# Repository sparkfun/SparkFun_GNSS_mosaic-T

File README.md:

SparkFun Timing GNSS Breakout - mosaic-T
========================================

[*SparkFun Timing GNSS Breakout - mosaic-T (GPS-28731)*](https://www.sparkfun.com/sparkfun-timing-gnss-breakout-mosaic-t.html)

At the heart of our Timing GNSS Breakout is [Septentrio](https://www.septentrio.com/en)'s mosaic-T, a compact, ultra-low power, multi-band, multi-constellation, high-precision GNSS timing receiver. It can acheive a timing precision of 5ns (5 billionths of a second), or better than 1ns with an optional subscription to the Fugro AtomiChron® L-band timing service. Event accuracy is better than 20ns. It also features Septentrio's unique [AIM+ technology](https://www.septentrio.com/en/learn-more/advanced-positioning-technology/aim-jamming-protection) for interference mitigation and anti-spoofing, ensuring best-in-class reliability and accuracy.

This board provides easy access to the mosaic-T's reference clock. Want to create your own disciplined oscillator? With this board you can. You can use the `RxClkBias` from the mosaic-T `PVTCartesian` or `PVTGeodetic` SBF messages to discipline your own 10MHz oscillator. The *EXT REF* connector accepts 50 Ohm 10MHz signals in the range -14dBm (min) to +14dBm (max). The *INT EXT* slide switch selects the internal or external oscillator.

The mosaic-T is a sophisticated timing receiver running an internal web server that can be accessed through the USB interface with a standard browser using a Linux/Windows computer. Septentrio also provides dozens of [video tutorials](https://www.youtube.com/@SeptentrioGNSS/videos) to guide users through the configuration settings of their GNSS receivers utilizing the web interface.

Beyond the capabilities of the mosaic-T module, this board is seamless to operate with no programming skills required. Gone are the times when a microcontroller was required to interface with the GNSS receiver and log data to an SD card and when users had to carry around an SD card reader to extract the data from the SD card. The Timing GNSS Breakout - mosaic-T  can start/stop logging data or mount/unmount the SD card, without a single line of code, just utilizing a simple button. For the users who prefer a command-line interface, Septentrio has you covered. Users can still control and configure the mosaic-T module through a CLI, which is useful for scenarios such as production line testing *(in fact, that is how we tested this board)*.

This breakout board is a perfect middle ground for users who would like to integrate the mosaic-T module into a project/enclosure with access to a majority of the module's available pins, similar to Septentrio's developer kit, but in the smaller form factor of their evaluation kit. Or maybe... you just needed a very accurate PPS output at a 3.3V logic level. *Please, check out our [hookup guide](https://docs.sparkfun.com/SparkFun_GNSS_mosaic-T) for more details on the capabilities of this board (that we couldn't fit in this product description).*

> [!CAUTION]
>
> RTK Not Supported
> --------------
> The mosaic-T is a superb GNSS module designed for highly accurate timing applications. **But it does not support RTK. It can not be configured as a RTK Rover or Base. RTCM output is not supported.**

Documentation
-------------

- **[Hookup Guide (mkdocs)](http://docs.sparkfun.com/SparkFun_GNSS_mosaic-T/)** - A hookup guide for the SparkFun mosaic-T Timing GNSS breakout board hosted by GitHub pages.<br>

Repository Contents
-------------------

- **[/docs](/docs/)** - Online documentation files
  - [/assets](/docs/assets/) - Assets files
    - [/3d_model](/docs/assets/3d_model/) - 3D models for the board
    - [/board_files](/docs/assets/board_files/) - Design files for the board
      - [KiCad Design Files](/docs/assets/board_files/kicad_files.zip) (.zip)
      - [Schematic](/docs/assets/board_files/schematic.pdf) (.pdf)
      - [Dimensions](/docs/assets/board_files/dimensions.pdf) (.pdf)
    - [/component_documentation](/docs/assets/component_documentation/) - Datasheets for hardware components
    - [/img/hookup_guide](/docs/assets/img/hookup_guide/) - Images for hookup guide documentation - Hookup guide images for the board
    - /Hardware - Hardware design files (.brd, .sch)
      - /Production - Production files

Product Variants
----------------

- mosaic-T:
  - [GPS-28731](https://www.sparkfun.com/sparkfun-timing-gnss-breakout-mosaic-t.html) - mosaic-T Timing GNSS Breakout
  - [SXT](https://www.sparkpnt.com/products/sxt-gnssdo) - GNSS Disciplined Oscillator
- mosaic-X5:
  - [GPS-23088](https://www.sparkfun.com/sparkfun-triband-gnss-rtk-breakout-mosaic-x5.html) - Triband GNSS RTK Breakout - mosaic-X5
  - [SXM-E](https://www.sparkpnt.com/products/sparkpnt-sxm-e-cors) - RTK mosaic-X5
  - [GPS-24903](https://www.sparkfun.com/sparkpnt-rtk-facet-mosaic-l-band.html) - SparkPNT RTK Facet mosaic L-Band
  - Flex Modules:
    - [GPS-28138](https://www.sparkfun.com/sparkpnt-gnss-flex-module-mosaic-x5.html) - GNSS Flex module - mosaic-X5
    - [GPS-29457](https://www.sparkfun.com/sparkpnt-gnss-flex-module-mosaic-x5-im19-imu.html) - GNSS Flex module - mosaic-X5 & IM19
    - [GPS-28766](https://www.sparkfun.com/sparkfun-gnss-flex-phat-mosaic-x5.html) - GNSS Flex pHAT w/ the mosaic-X5 GNSS Flex module
    - [GPS-29889](https://www.sparkfun.com/sparkfun-gnss-flex-phat-mosaic-x5-im19-imu.html) - GNSS Flex pHAT w/ the mosaic-X5 & IM19 GNSS Flex module
- mosaic-G5 P3:
  - [GPS-29208]( - GNSS RTK Breakout - mosaic-G5 P3
  - Flex Modules:
    - [GPS-29209](https://www.sparkfun.com/sparkpnt-gnss-flex-module-mosaic-g5-p3.html) - GNSS Flex module - mosaic-G5 P3
    - [GPS-29363](https://www.sparkfun.com/sparkpnt-gnss-flex-module-mosaic-g5-p3-im19-imu.html) - GNSS Flex module - mosaic-G5 P3 & IM19
    - [GPS-](https://www.sparkfun.com/sparkfun-gnss-flex-phat-mosaic-g5-p3.html) - GNSS Flex pHAT w/ the mosaic-G5 P3 GNSS Flex module
    - [GPS-](https://www.sparkfun.com/sparkfun-gnss-flex-phat-mosaic-g5-p3-im19-imu.html) - GNSS Flex pHAT w/ the mosaic-G5 P3 & IM19 GNSS Flex module

Version History
---------------

- [v10](https://github.com/sparkfun/SparkFun_GNSS_mosaic-T/releases/tag/v10) - Initial Release

License Information
-------------------

This product is ***open source***!

Please review the [`LICENSE.md`](./LICENSE.md) file for license information.

If you have any questions or concerns about licensing, please contact technical support on our [SparkFun forums](https://community.sparkfun.com/).

Distributed as-is; no warranty is given.

- Your friends at SparkFun.

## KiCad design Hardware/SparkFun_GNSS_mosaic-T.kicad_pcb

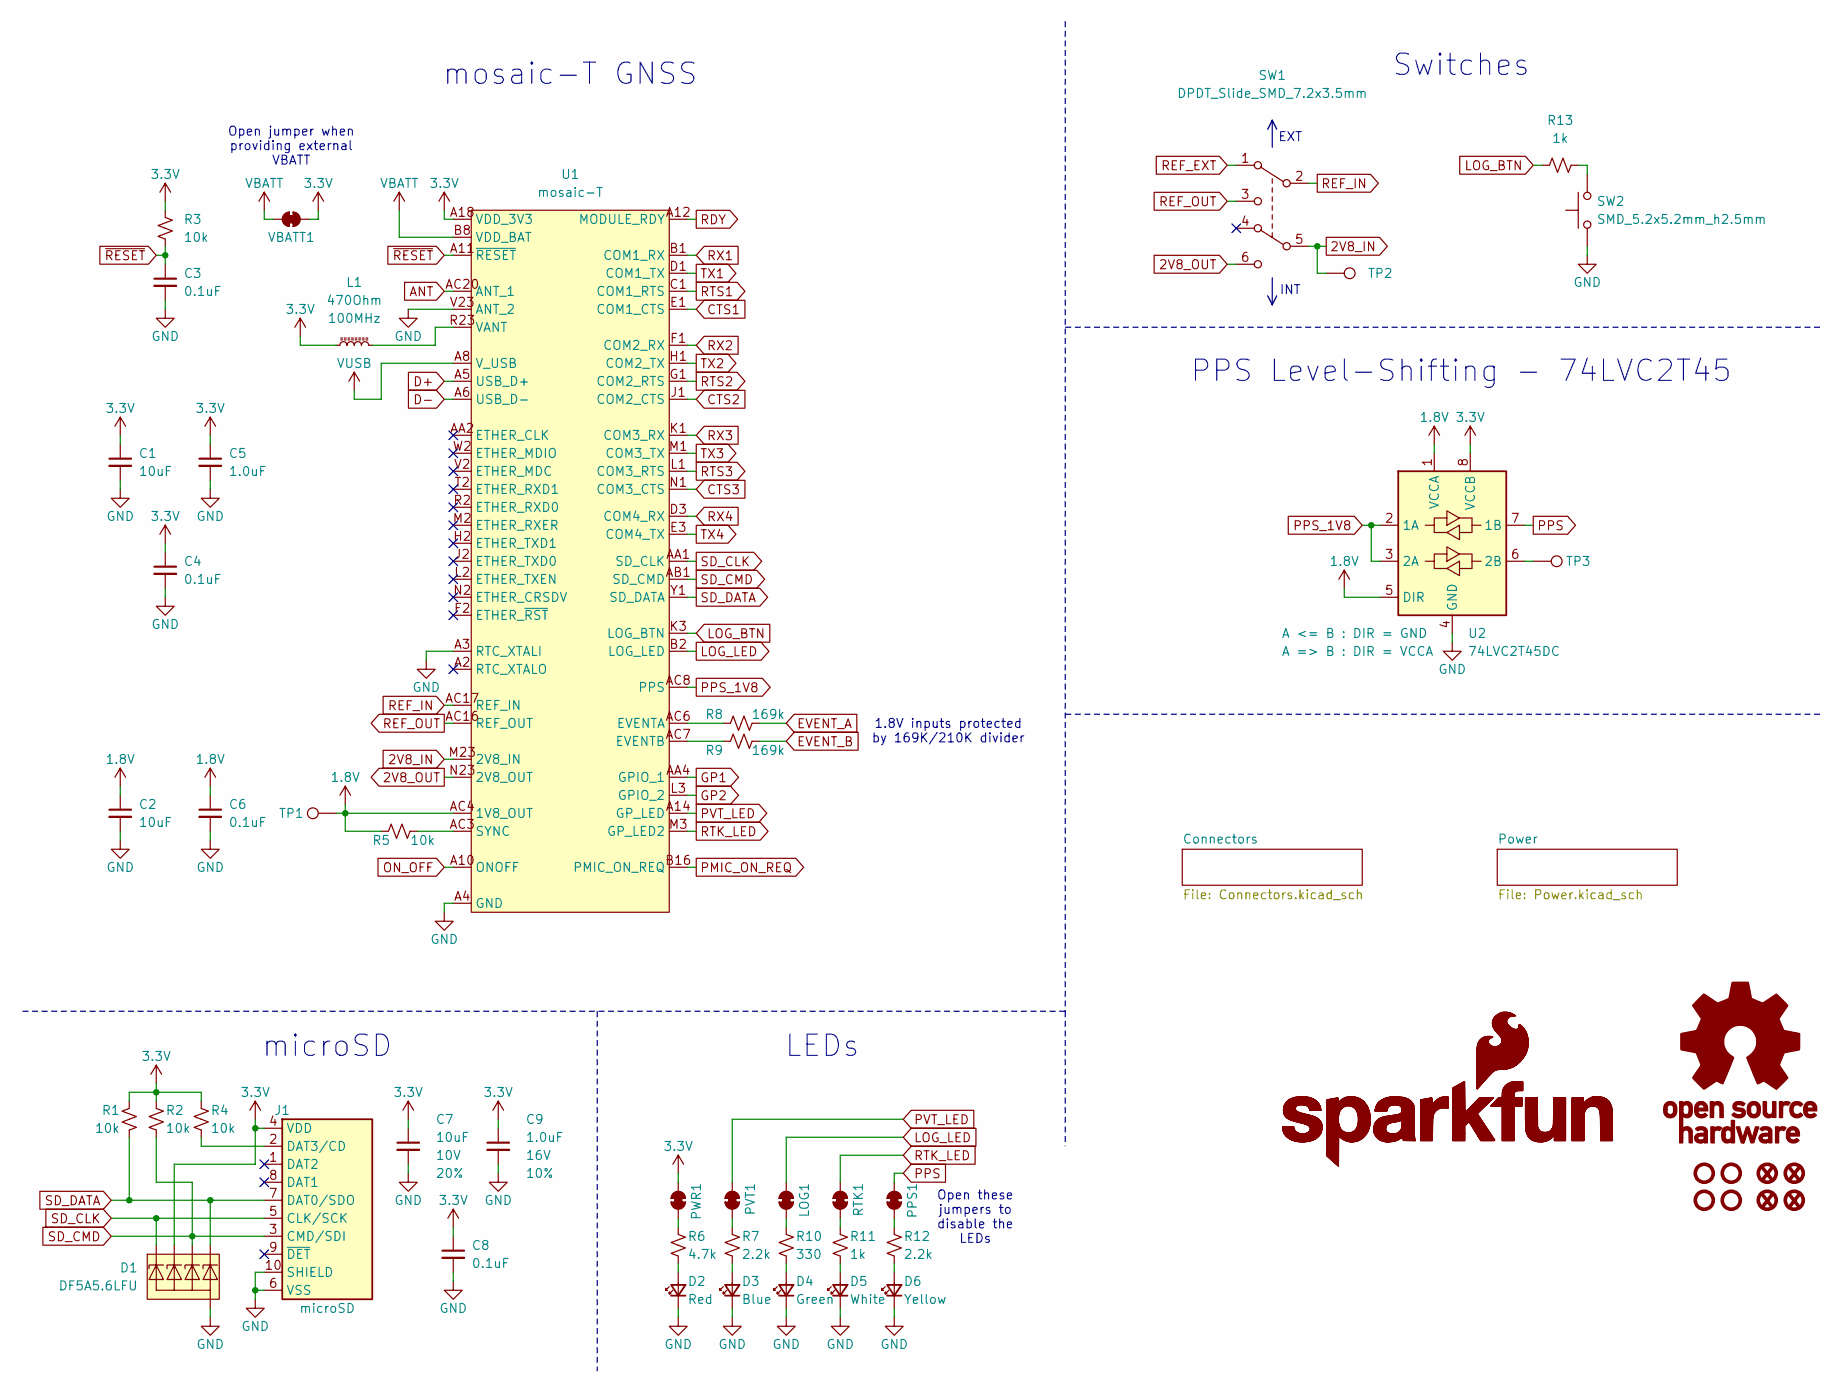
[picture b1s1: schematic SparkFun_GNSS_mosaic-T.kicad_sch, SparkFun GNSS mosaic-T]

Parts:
C1, C2, C7: 10uF; C_0603_1608Metric; Voltage 10V; Tolerance 20%
C3, C4, C6, C8: 0.1uF; C_0603_1608Metric; Voltage 25V; Tolerance 20%
C5, C9: 1.0uF; C_0603_1608Metric; Voltage 16V; Tolerance 10%
D1: DF5A5.6LFU; SOT-353
D2: Red; LED_0603_1608Metric_Red
D3: Blue; LED_0603_1608Metric_Blue
D4: Green; LED_0603_1608Metric_Green
D5: White; LED_0603_1608Metric_White
D6: Yellow; LED_0603_1608Metric_Yellow
FID1, FID2, FID3, FID4: Fiducial_0.5mm; Fiducial_0.5mm_Mask1mm
G1, G2: SparkFun_Logo
G3: OSHW_Logo; Creative_Commons_License
J1: microSD; microSD_External_Pin
L1: 470Ohm; C_0603_1608Metric
LOG1: Jumper_2_NC_Trace
PPS1: Jumper_2_NC_Trace
PVT1: Jumper_2_NC_Trace
PWR1: Jumper_2_NC_Trace
R1, R2, R3, R4, R5: 10k; R_0603_1608Metric
R6: 4.7k; R_0603_1608Metric
R7, R12: 2.2k; R_0603_1608Metric
R8, R9: 169k; R_0603_1608Metric
R10: 330; R_0603_1608Metric
R11, R13: 1k; R_0603_1608Metric
RTK1: Jumper_2_NC_Trace
ST1, ST2, ST3, ST4: Standoff
SW1: DPDT_Slide_SMD_7.2x3.5mm; Slide_DPDT_SMD_7.2x3.5mm; Mfg Part# ABC
SW2: SMD_5.2x5.2mm_h2.5mm; Push_SMD_5.2x5.2mm_h2.5mm
TP1, TP2, TP3: 1.25mm; TestPoint-1.25mm
U1: mosaic-T; MOSAIC_LGA
U2: 74LVC2T45DC; VSSOP8_SOT765-1
VBATT1: Jumper_2_NC_Trace

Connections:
1.8V: C2.1, C6.1, R5.1, TP1.1, U1.AC4 (1V8_OUT), U2.1 (VCCA), U2.5 (DIR); also elsewhere on the board
2V8_IN: SW1.5 (B), TP2.1, U1.M23 (2V8_IN)
2V8_OUT: SW1.6 (C), U1.N23 (2V8_OUT)
3.3V: C1.1, C4.1, C5.1, C7.1, C8.1, C9.1, D1.3 (K2), J1.4 (VDD), L1.1, PWR1.2 (B), R1.2, R2.2, R3.2, R4.2, U1.A18 (VDD_3V3), U1.A19 (VDD_3V3), U1.A20 (VDD_3V3), U1.B18 (VDD_3V3), U1.B19 (VDD_3V3), U1.B20 (VDD_3V3), U1.C18 (VDD_3V3), U1.C19 (VDD_3V3), U1.C20 (VDD_3V3), U2.8 (VCCB), VBATT1.1 (A); also elsewhere on the board
ANT: U1.AC20 (ANT_1); also elsewhere on the board
CTS1: U1.E1 (COM1_CTS); also elsewhere on the board
CTS2: U1.J1 (COM2_CTS); also elsewhere on the board
CTS3: U1.N1 (COM3_CTS); also elsewhere on the board
D+: U1.A5 (USB_D+); also elsewhere on the board
D-: U1.A6 (USB_D-); also elsewhere on the board
EVENT_A: R8.2; also elsewhere on the board
EVENT_B: R9.2; also elsewhere on the board
GND: C1.2, C2.2, C3.2, C4.2, C5.2, C6.2, C7.2, C8.2, C9.2, D1.2 (A), D2.1 (K), D3.1 (K), D4.1 (K), D5.1 (K), D6.1 (K), J1.6 (VSS), J1.10 (SHIELD), SW2.1, U1.A3 (RTC_XTALI), U1.A4 (GND), U1.A7 (GND), U1.A15 (GND), U1.A16 (GND), U1.A17 (GND), U1.A21 (GND), U1.A22 (GND), U1.A23 (GND), U1.AA13 (GND), U1.AA14 (GND), U1.AA15 (GND), U1.AA16 (GND), U1.AA17 (GND), U1.AA18 (GND), U1.AA19 (GND), U1.AA20 (GND), U1.AA21 (GND), U1.AA22 (GND), U1.AA23 (GND), U1.AB2 (GND), U1.AB3 (GND), U1.AB4 (GND), U1.AB5 (GND), U1.AB6 (GND), U1.AB7 (GND), U1.AB8 (GND), U1.AB13 (GND), U1.AB14 (GND), U1.AB15 (GND), U1.AB16 (GND), U1.AB17 (GND), U1.AB18 (GND), U1.AB19 (GND), U1.AB20 (GND), U1.AB21 (GND), U1.AB22 (GND), U1.AB23 (GND), U1.AC13 (GND), U1.AC15 (GND), U1.AC18 (GND), U1.AC19 (GND), U1.AC21 (GND), U1.AC22 (GND), U1.AC23 (GND), U1.B4 (GND), U1.B5 (GND), U1.B6 (GND), U1.B7 (GND), U1.B13 (GND), U1.B17 (GND), U1.B21 (GND), U1.C4 (GND), U1.C7 (GND), U1.C15 (GND), U1.C16 (GND), U1.C17 (GND), U1.C23 (GND), U1.D2 (GND), U1.D21 (GND), U1.D22 (GND), U1.D23 (GND), U1.E2 (GND), U1.E21 (GND), U1.E22 (GND), U1.E23 (GND), U1.F21 (GND), U1.F22 (GND), U1.F23 (GND), U1.G2 (GND), U1.G21 (GND), U1.G23 (GND), U1.H21 (GND), U1.H22 (GND), U1.H23 (GND), U1.J21 (GND), U1.J22 (GND), U1.J23 (GND), U1.K2 (GND), U1.K21 (GND), U1.K22 (GND), U1.K23 (GND), U1.L21 (GND), U1.L22 (GND), U1.L23 (GND), U1.M21 (GND), U1.M22 (GND), U1.N21 (GND), U1.N22 (GND), U1.P1 (GND), U1.P2 (GND), U1.P3 (GND), U1.P21 (GND), U1.P22 (GND), U1.R3 (GND), U1.R21 (GND), U1.R22 (GND), U1.T21 (GND), U1.T22 (GND), U1.T23 (GND), U1.U2 (GND), U1.U21 (GND), U1.U22 (GND), U1.U23 (GND), U1.V21 (GND), U1.V22 (GND), U1.V23 (ANT_2), U1.W21 (GND), U1.W22 (GND), U1.W23 (GND), U1.Y2 (GND), U1.Y21 (GND), U1.Y22 (GND), U1.Y23 (GND), U2.4 (GND); also elsewhere on the board
GP1: U1.AA4 (GPIO_1); also elsewhere on the board
GP2: U1.L3 (GPIO_2); also elsewhere on the board
LOG_BTN: R13.2, U1.K3 (LOG_BTN); also elsewhere on the board
LOG_LED: LOG1.2 (B), U1.B2 (LOG_LED); also elsewhere on the board
unnamed: D2.2 (A), R6.1
unnamed: D3.2 (A), R7.1
unnamed: D4.2 (A), R10.1
unnamed: D5.2 (A), R11.1
unnamed: D6.2 (A), R12.1
unnamed: J1.2 (DAT3/CD), R4.1
unnamed: LOG1.1 (A), R10.2
unnamed: PPS1.1 (A), R12.2
unnamed: PVT1.1 (A), R7.2
unnamed: PWR1.1 (A), R6.2
unnamed: R13.1, SW2.2
unnamed: R11.2, RTK1.1 (A)
unnamed: R8.1, U1.AC6 (EVENTA)
unnamed: R9.1, U1.AC7 (EVENTB)
unnamed: R5.2, U1.AC3 (SYNC)
unnamed: TP3.1, U2.6 (2B)
ON_OFF: U1.A10 (ONOFF); also elsewhere on the board
PMIC_ON_REQ: U1.B16 (PMIC_ON_REQ); also elsewhere on the board
PPS: PPS1.2 (B), U2.7 (1B); also elsewhere on the board
PPS_1V8: U1.AC8 (PPS), U2.2 (1A), U2.3 (2A)
PVT_LED: PVT1.2 (B), U1.A14 (GP_LED); also elsewhere on the board
RDY: U1.A12 (MODULE_RDY); also elsewhere on the board
REF_EXT: SW1.1 (A); also elsewhere on the board
REF_IN: SW1.2 (B), U1.AC17 (REF_IN)
REF_OUT: SW1.3 (C), U1.AC16 (REF_OUT)
RTK_LED: RTK1.2 (B), U1.M3 (GP_LED2); also elsewhere on the board
RTS1: U1.C1 (COM1_RTS); also elsewhere on the board
RTS2: U1.G1 (COM2_RTS); also elsewhere on the board
RTS3: U1.L1 (COM3_RTS); also elsewhere on the board
RX1: U1.B1 (COM1_RX); also elsewhere on the board
RX2: U1.F1 (COM2_RX); also elsewhere on the board
RX3: U1.K1 (COM3_RX); also elsewhere on the board
RX4: U1.D3 (COM4_RX); also elsewhere on the board
SD_CLK: D1.1 (K1), J1.5 (CLK/SCK), U1.AA1 (SD_CLK)
SD_CMD: D1.4 (K3), J1.3 (CMD/SDI), R2.1, U1.AB1 (SD_CMD)
SD_DATA: D1.5 (K4), J1.7 (DAT0/SDO), R1.1, U1.Y1 (SD_DATA)
TX1: U1.D1 (COM1_TX); also elsewhere on the board
TX2: U1.H1 (COM2_TX); also elsewhere on the board
TX3: U1.M1 (COM3_TX); also elsewhere on the board
TX4: U1.E3 (COM4_TX); also elsewhere on the board
VANT: L1.2, U1.P23 (VANT), U1.R23 (VANT)
VBATT: U1.B8 (VDD_BAT), VBATT1.2 (B); also elsewhere on the board
VUSB: U1.A8 (V_USB); also elsewhere on the board
~RESET: C3.1, R3.1, U1.A11 (~RESET); also elsewhere on the board

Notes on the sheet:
LEDs
PPS Level-Shifting - 74LVC2T45
Open jumper when providing external VBATT
mosaic-T GNSS
Switches
Open these jumpers to disable the LEDs
microSD
EXT
1.8V inputs protected by 169K/210K divider
INT

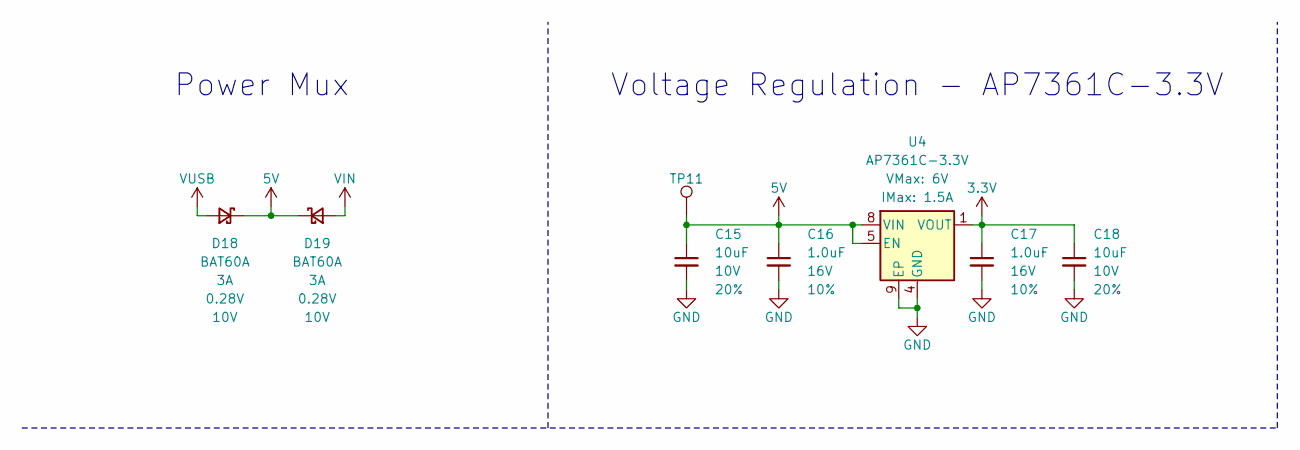
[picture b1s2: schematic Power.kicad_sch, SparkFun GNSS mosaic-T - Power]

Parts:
C15, C18: 10uF; C_0603_1608Metric; Voltage 10V; Tolerance 20%
C16, C17: 1.0uF; C_0603_1608Metric; Voltage 16V; Tolerance 10%
D18, D19: BAT60A; SOD-323
TP11: 1.25mm; TestPoint-1.25mm
U4: AP7361C-3.3V; UDFN-8

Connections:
3.3V: C17.1, C18.1, U4.1 (VOUT); also elsewhere on the board
5V: C15.1, C16.1, D18.1 (K), D19.1 (K), TP11.1, U4.5 (EN), U4.8 (VIN); also elsewhere on the board
GND: C15.2, C16.2, C17.2, C18.2, U4.4 (GND), U4.9 (EP); also elsewhere on the board
VIN: D19.2 (A); also elsewhere on the board
VUSB: D18.2 (A); also elsewhere on the board

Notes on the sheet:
Power Mux
Voltage Regulation - AP7361C-3.3V

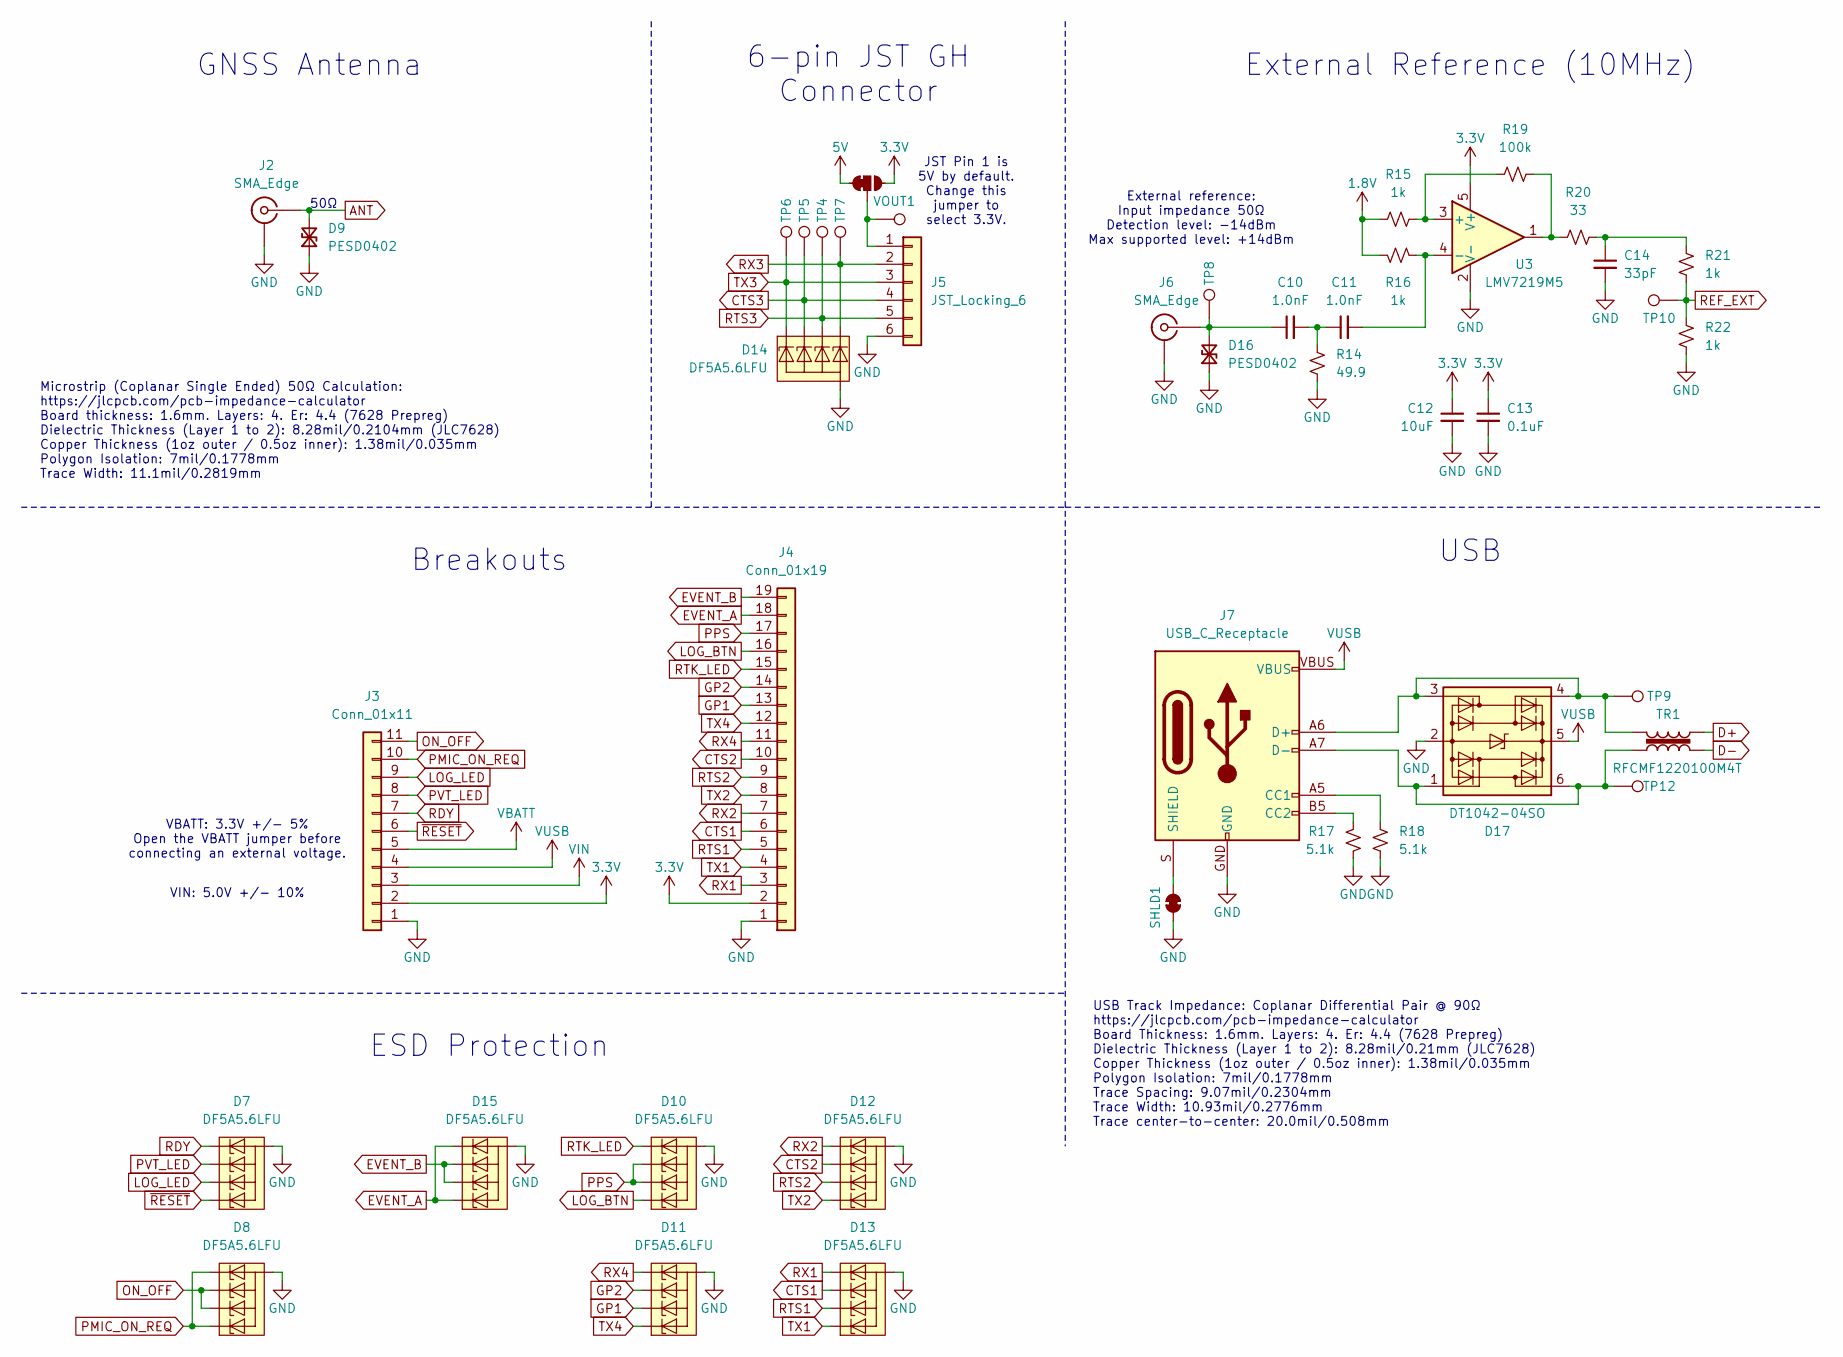
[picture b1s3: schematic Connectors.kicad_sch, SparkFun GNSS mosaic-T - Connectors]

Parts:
C10, C11: 1.0nF; C_0603_1608Metric; Voltage 50V; Tolerance 10%
C12: 10uF; C_0603_1608Metric; Voltage 10V; Tolerance 20%
C13: 0.1uF; C_0603_1608Metric; Voltage 25V; Tolerance 20%
C14: 33pF; C_0603_1608Metric; Voltage 50V; Tolerance 5%
D7, D8, D10, D11, D12, D13, D14, D15: DF5A5.6LFU; SOT-353
D9, D16: PESD0402; C_0402_1005Metric
D17: DT1042-04SO; SOT23-6
J2, J6: SMA_Edge
J3: Conn_01x11; 1x11
J4: Conn_01x19; 1x19
J5: JST_Locking_6; JST_SMD_1.25mm-6_Locking
J7: USB_C_Receptacle; USB-C_16
R14: 49.9; R_0603_1608Metric; Tolerance 1%
R15, R16, R21, R22: 1k; R_0603_1608Metric
R17, R18: 5.1k; R_0603_1608Metric
R19: 100k; R_0603_1608Metric
R20: 33; R_0603_1608Metric
SHLD1: Jumper_2_NC_Trace
TP4, TP5, TP6, TP7, TP8, TP9, TP10, TP12, TP13: 1.25mm; TestPoint-1.25mm
TR1: RFCMF1220100M4T
U3: LMV7219M5; SOT23-5
VOUT1: Jumper_3_NC-1_Trace

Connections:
1.8V: R15.2, R16.2; also elsewhere on the board
3.3V: C12.1, C13.1, J3.2, J4.2, U3.5 (V+), VOUT1.3 (C); also elsewhere on the board
5V: VOUT1.1 (A); also elsewhere on the board
ANT: D9.2 (A2), J2.1 (In); also elsewhere on the board
CTS1: D13.4 (K3), J4.6; also elsewhere on the board
CTS2: D12.4 (K3), J4.10; also elsewhere on the board
CTS3: D14.3 (K2), J5.4, TP5.1; also elsewhere on the board
D+: TR1.4; also elsewhere on the board
D-: TR1.2; also elsewhere on the board
EVENT_A: D15.1 (K1), D15.5 (K4), J4.18; also elsewhere on the board
EVENT_B: D15.3 (K2), D15.4 (K3), J4.19; also elsewhere on the board
GND: C12.2, C13.2, C14.2, D7.2 (A), D8.2 (A), D9.1 (A1), D10.2 (A), D11.2 (A), D12.2 (A), D13.2 (A), D14.2 (A), D15.2 (A), D16.1 (A1), D17.2 (GND), J2.2 (Ext), J3.1, J4.1, J5.6, J6.2 (Ext), J7.GND, R14.1, R17.1, R18.1, R22.2, SHLD1.1 (A), U3.2 (V-); also elsewhere on the board
GP1: D11.3 (K2), J4.13; also elsewhere on the board
GP2: D11.4 (K3), J4.14; also elsewhere on the board
LOG_BTN: D10.1 (K1), J4.16; also elsewhere on the board
LOG_LED: D7.3 (K2), J3.9; also elsewhere on the board
unnamed: C10.2, C11.1, R14.2
unnamed: C14.1, R20.2, R21.1
unnamed: C10.1, D16.2 (A2), J6.1 (In), TP8.1
unnamed: D17.1 (I/O1), D17.6 (I/O4), J7.A7 (D-), J7.B7 (D-), TP12.1, TR1.1
unnamed: D17.3 (I/O2), D17.4 (I/O3), J7.A6 (D+), J7.B6 (D+), TP9.1, TR1.3
unnamed: J5.1, TP13.1, VOUT1.2 (B)
unnamed: J7.A5 (CC1), R18.2
unnamed: J7.B5 (CC2), R17.2
unnamed: J7.S (SHIELD), SHLD1.2 (B)
unnamed: R19.2, R20.1, U3.1
unnamed: R15.1, R19.1, U3.3 (+)
unnamed: C11.2, R16.1, U3.4 (-)
ON_OFF: D8.3 (K2), D8.4 (K3), J3.11; also elsewhere on the board
PMIC_ON_REQ: D8.1 (K1), D8.5 (K4), J3.10; also elsewhere on the board
PPS: D10.3 (K2), D10.4 (K3), J4.17; also elsewhere on the board
PVT_LED: D7.4 (K3), J3.8; also elsewhere on the board
RDY: D7.5 (K4), J3.7; also elsewhere on the board
REF_EXT: R21.2, R22.1, TP10.1; also elsewhere on the board
RTK_LED: D10.5 (K4), J4.15; also elsewhere on the board
RTS1: D13.3 (K2), J4.5; also elsewhere on the board
RTS2: D12.3 (K2), J4.9; also elsewhere on the board
RTS3: D14.4 (K3), J5.5, TP4.1; also elsewhere on the board
RX1: D13.5 (K4), J4.3; also elsewhere on the board
RX2: D12.5 (K4), J4.7; also elsewhere on the board
RX3: D14.5 (K4), J5.2, TP7.1; also elsewhere on the board
RX4: D11.5 (K4), J4.11; also elsewhere on the board
TX1: D13.1 (K1), J4.4; also elsewhere on the board
TX2: D12.1 (K1), J4.8; also elsewhere on the board
TX3: D14.1 (K1), J5.3, TP6.1; also elsewhere on the board
TX4: D11.1 (K1), J4.12; also elsewhere on the board
VBATT: J3.5; also elsewhere on the board
VIN: J3.3; also elsewhere on the board
VUSB: D17.5 (VCC), J3.4, J7.VBUS; also elsewhere on the board
~RESET: D7.1 (K1), J3.6; also elsewhere on the board

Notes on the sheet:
Breakouts
USB Track Impedance: Coplanar Differential Pair @ 90Ω https://jlcpcb.com/pcb-impedance-calculator Board Thickness: 1.6mm. Layers: 4. Er: 4.4 (7628 Prepreg) Dielectric Thickness (Layer 1 to 2): 8.28mil/0.21mm (JLC7628) Copper Thickness (1oz outer / 0.5oz inner): 1.38mil/0.035mm Polygon Isolation: 7m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
50Ω
GNSS Antenna
JST Pin 1 is 5V by default. Change this jumper to select 3.3V.
USB
External Reference (10MHz)
Microstrip (Coplanar Single Ended) 50Ω Calculation: https://jlcpcb.com/pcb-impedance-calculator Board thickness: 1.6mm. Layers: 4. Er: 4.4 (7628 Prepreg) Dielectric Thickness (Layer 1 to 2): 8.28mil/0.2104mm (JLC7628) Copper Thickness (1oz outer / 0.5oz inner): 1.38mil/0.035mm Polygon Isolation: 7m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
6-pin JST GH Connector
ESD Protection
VBATT: 3.3V +/- 5% Open the VBATT jumper before connecting an external voltage.
VIN: 5.0V +/- 10%
External reference: Input impedance 50Ω Detection level: -14dBm Max supported level: +14dBm

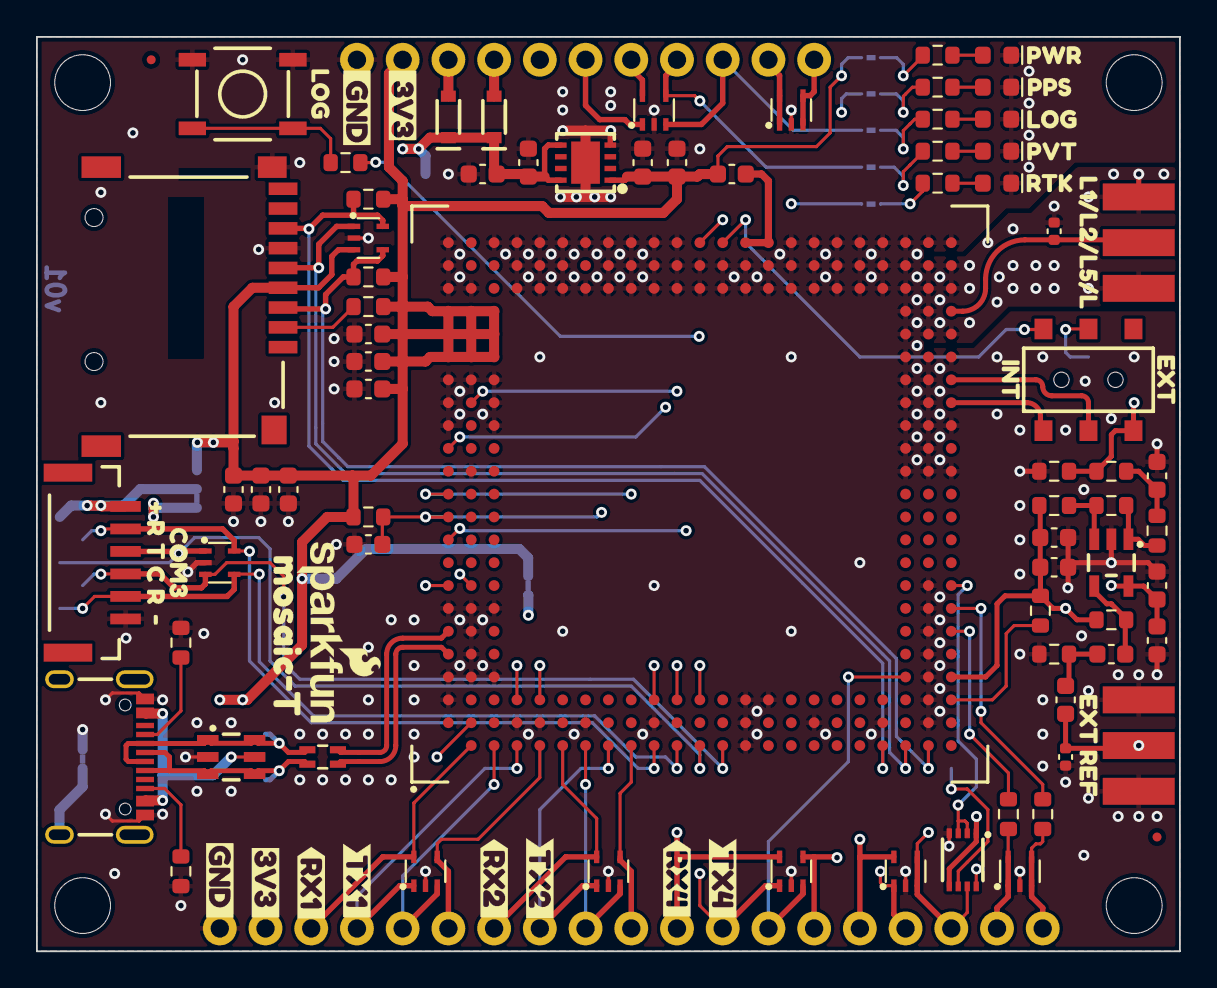
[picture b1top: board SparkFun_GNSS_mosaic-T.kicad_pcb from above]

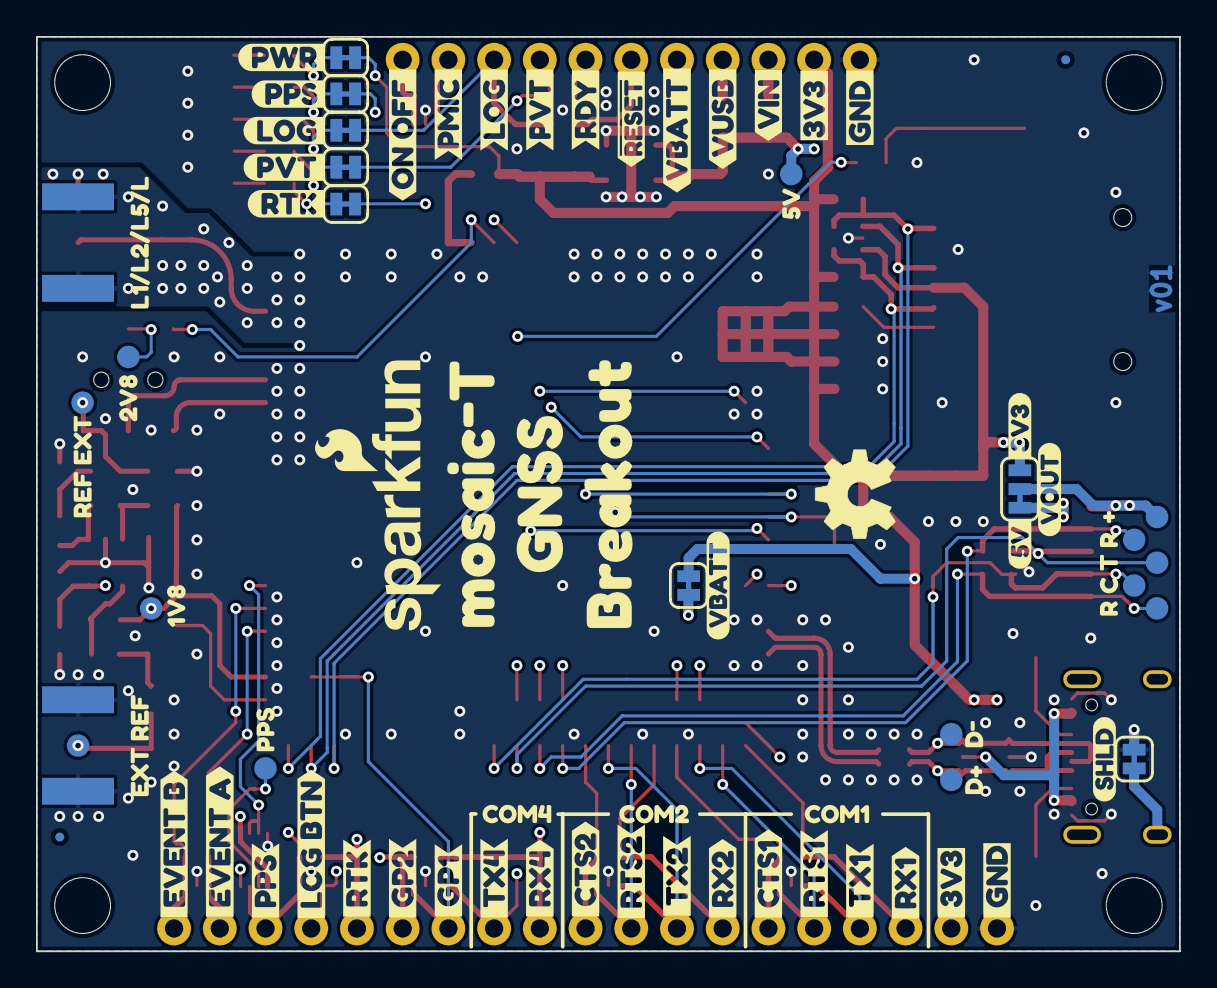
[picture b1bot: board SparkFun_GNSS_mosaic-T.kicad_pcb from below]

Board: 4 copper layers, 63.5 x 50.8 mm, 193 parts (84 on the bottom side), 75 nets.

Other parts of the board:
Ref**: Val**; OSHW_Logo_5mm
kibuzzard-67D03C98, kibuzzard-67D03C98#2: G***; kibuzzard-67D03C98
kibuzzard-67D03CC5, kibuzzard-67D03CC5#2: G***; kibuzzard-67D03CC5
kibuzzard-67D04A61: G***; kibuzzard-67D04A61
kibuzzard-67D04A72: G***; kibuzzard-67D04A72
kibuzzard-67D04A80: G***; kibuzzard-67D04A80
kibuzzard-67D04A91: G***; kibuzzard-67D04A91
kibuzzard-67D04AA3: G***; kibuzzard-67D04AA3
kibuzzard-67D04B0C: G***; kibuzzard-67D04B0C
kibuzzard-67D04B28: G***; kibuzzard-67D04B28
kibuzzard-67D04B58: G***; kibuzzard-67D04B58
kibuzzard-67D04B80: G***; kibuzzard-67D04B80
kibuzzard-67D04D07: G***; kibuzzard-67D04D07
kibuzzard-67D04D20: G***; kibuzzard-67D04D20
kibuzzard-67D04D30: G***; kibuzzard-67D04D30
kibuzzard-67D04D50: G***; kibuzzard-67D04D50
kibuzzard-67D04D99: G***; kibuzzard-67D04D99
kibuzzard-67D04E6C: G***; kibuzzard-67D04E6C
kibuzzard-67D04E18: G***; kibuzzard-67D04E18
kibuzzard-67D04E88: G***; kibuzzard-67D04E88
kibuzzard-67D04E93: G***; kibuzzard-67D04E93
kibuzzard-67D04EAA: G***; kibuzzard-67D04EAA
kibuzzard-67D04FB5: G***; kibuzzard-67D04FB5
kibuzzard-67D022A2: G***; kibuzzard-67D022A2
kibuzzard-67D022AC: G***; kibuzzard-67D022AC
kibuzzard-67D035E7: G***; kibuzzard-67D035E7
kibuzzard-67D035FF: G***; kibuzzard-67D035FF
kibuzzard-67D044A8: G***; kibuzzard-67D044A8
kibuzzard-67D044BC: G***; kibuzzard-67D044BC
kibuzzard-67D044ED: G***; kibuzzard-67D044ED
kibuzzard-67D045AD: G***; kibuzzard-67D045AD
kibuzzard-67D045C9: G***; kibuzzard-67D045C9
kibuzzard-67D045EC: G***; kibuzzard-67D045EC
kibuzzard-67D046A8: G***; kibuzzard-67D046A8
kibuzzard-67D046B5: G***; kibuzzard-67D046B5
kibuzzard-67D046BD: G***; kibuzzard-67D046BD
kibuzzard-67D046CC: G***; kibuzzard-67D046CC
kibuzzard-67D046F7: G***; kibuzzard-67D046F7
kibuzzard-67D046FF: G***; kibuzzard-67D046FF
kibuzzard-67D047AD: G***; kibuzzard-67D047AD
kibuzzard-67D047C3: G***; kibuzzard-67D047C3
kibuzzard-67D047D9: G***; kibuzzard-67D047D9
kibuzzard-67D047EC: G***; kibuzzard-67D047EC
kibuzzard-67D049A2, kibuzzard-67D049A2#2: G***; kibuzzard-67D049A2
kibuzzard-67D049B0, kibuzzard-67D049B0#2: G***; kibuzzard-67D049B0
kibuzzard-67D171AB: G***; kibuzzard-67D171AB
kibuzzard-67D171E5: G***; kibuzzard-67D171E5
kibuzzard-67D0352E: G***; kibuzzard-67D0352E
kibuzzard-67D0356E: G***; kibuzzard-67D0356E
kibuzzard-67D0451A: G***; kibuzzard-67D0451A
kibuzzard-67D0454D: G***; kibuzzard-67D0454D
kibuzzard-67D0455C: G***; kibuzzard-67D0455C
kibuzzard-67D0474E: G***; kibuzzard-67D0474E
kibuzzard-67D1674C: G***; kibuzzard-67D1674C
kibuzzard-67D02274: G***; kibuzzard-67D02274
kibuzzard-67D02289: G***; kibuzzard-67D02289
kibuzzard-67D02298, kibuzzard-67D02298#2: G***; kibuzzard-67D02298
kibuzzard-67D03557: G***; kibuzzard-67D03557
kibuzzard-67D03584: G***; kibuzzard-67D03584
kibuzzard-67D04501: G***; kibuzzard-67D04501
kibuzzard-67D04530: G***; kibuzzard-67D04530
kibuzzard-67D04570: G***; kibuzzard-67D04570
kibuzzard-67D04579: G***; kibuzzard-67D04579
kibuzzard-67D04612: G***; kibuzzard-67D04612
kibuzzard-67D04639: G***; kibuzzard-67D04639
kibuzzard-67D04669: G***; kibuzzard-67D04669
kibuzzard-67D04726: G***; kibuzzard-67D04726
kibuzzard-67D04771: G***; kibuzzard-67D04771
kibuzzard-67D04943: G***; kibuzzard-67D04943
kibuzzard-67D04998, kibuzzard-67D04998#2, kibuzzard-67D04998#3, kibuzzard-67D04998#4: G***; kibuzzard-67D04998
kibuzzard-67D05112: G***; kibuzzard-67D05112
kibuzzard-67D05125: G***; kibuzzard-67D05125
kibuzzard-67D16721: G***; kibuzzard-67D16721
kibuzzard-67D16775: G***; kibuzzard-67D16775
kibuzzard-67DABC7B: G***; kibuzzard-67DABC7B
kibuzzard-67DABC71: G***; kibuzzard-67DABC71
kibuzzard-67DABC87: G***; kibuzzard-67DABC87
kibuzzard-67DABED8: G***; kibuzzard-67DABED8
kibuzzard-67DAC0B5: G***; kibuzzard-67DAC0B5
kibuzzard-67DAC0E0: G***; kibuzzard-67DAC0E0
kibuzzard-67DAC106: G***; kibuzzard-67DAC106

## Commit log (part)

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2025-03-10 Schematic WIP
2025-03-11 Ready for airwire review
2025-03-12 Routing - WIP
2025-03-13 Routed
2025-03-13 CAMmed
2025-03-13 Re-panelized and CAMmed
2025-03-13 Re-panelize and CAM using released versions
2025-03-13 Add README
2025-03-13 Add docs
2025-03-19 Schematic updates after proto review
2025-03-19 More updates, post proto review
2025-03-19 Re-panelized after proto review
2025-03-19 Remove alternate "PowerPins"
2025-03-21 Re-panelized
2025-06-11 Docs - Initial Draft
2025-06-12 Update/Fix links
2025-06-12 Update mkdocs.yml
    Adjust section hierarchy
2025-06-12 Update rxtools.md
    Move annotation to admonition
    Remove and update footnotes
2025-06-12 Disciplined Oscillator
    Add instructions for creating disciplined oscillator
    Add missing image for assembly
2025-06-12 Fugro AtomiChron
    Add instructions for Fugro's AtomiChron service
2025-06-12 Add build workflow
2025-06-12 Deployed 1937847 with MkDocs version: 1.6.1
2025-06-12 Fix links
2025-06-12 Deployed 3ab6f21 with MkDocs version: 1.6.1
2025-06-12 Add QR images
2025-06-12 Add thumbnail image
2025-06-12 Remove product video links
2025-06-12 Deployed 987a278 with MkDocs version: 1.6.1
2025-06-14 Swap the SMA cable images
2025-06-14 Deployed 0119c0d with MkDocs version: 1.6.1
2025-06-14 Correct RTK references
2025-06-14 Deployed 4a9e27c with MkDocs version: 1.6.1
2025-07-13 Fix links
    Replaced all references to the SparkFun_GNSS_Flex_System repository with SparkFun_GNSS_mosaic-T
2025-07-13 Deployed 057ae07 with MkDocs version: 1.6.1
2025-09-10 Deployed b954f6c with MkDocs version: 1.6.1
2025-09-10 Deployed b89b3d3 with MkDocs version: 1.6.1
2025-09-10 Deployed 2cbb906 with MkDocs version: 1.6.1
2025-09-12 Deployed 3225dcc with MkDocs version: 1.6.1
2025-09-12 Update .gitignore
    Remove leftover merge conflict markers
    Consolidate duplicate entries
    Remove ignored file type
2025-09-12 Deployed 4bd5c57 with MkDocs version: 1.6.1
2025-09-12 Update footprint
    Fixes file path and position for the 3D model
2025-09-12 Update component documentation
    Updates the datasheet, firmware, manuals, etc. for the mosaic-T
2025-09-15 Deployed afe0695 with MkDocs version: 1.6.1
2025-09-15 Replace <center> tag
    Replace use of <center> tag to conform to HTML5 standards
2025-09-15 Deployed d724bb1 with MkDocs version: 1.6.1
2025-10-10 Update 3D model
    Better compression
2025-10-10 Fix styling
    Use single-line format for captions
2025-10-10 Remove section icons
2025-10-10 Update workflow
    Use requirements.txt to install dependencies
    Remove git-authors plugin
2025-10-10 Add template images
2025-10-10 Deployed 0ce12f5 with MkDocs version: 1.6.1
2026-06-03 Deployed f5ecb1d with MkDocs version: 1.6.1

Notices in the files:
parts and their libraries:
https://creativecommons.org/licenses/by-sa/4.0
Released under the Creative Commons Attribution Share-Alike 4.0 License
